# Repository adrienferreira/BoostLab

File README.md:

# BoostLab
DCDC step-down converter using only discrete components.

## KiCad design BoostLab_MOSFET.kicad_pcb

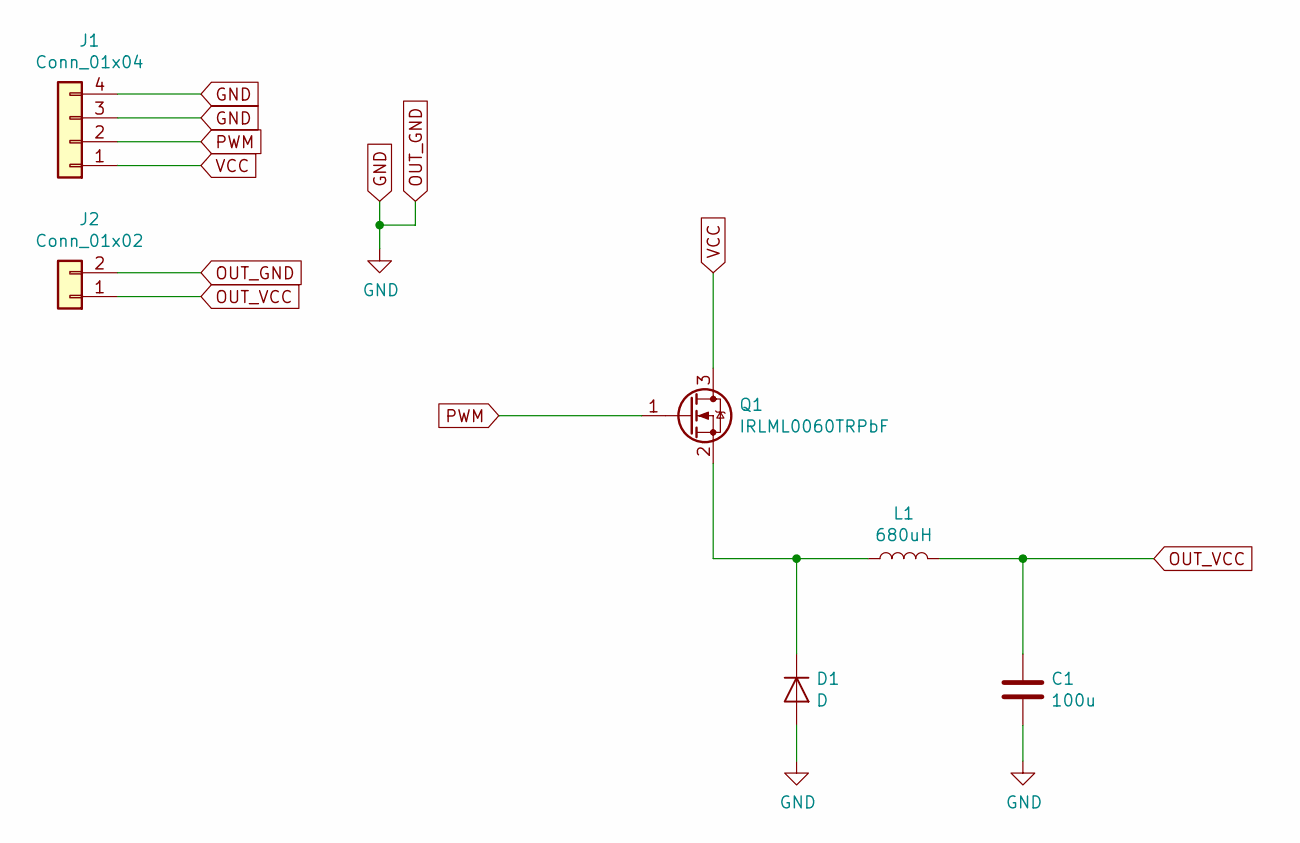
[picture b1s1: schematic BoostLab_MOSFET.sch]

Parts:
C1: 100u; C_1206_3216Metric_Pad1.42x1.75mm_HandSolder
D1: D; D_DO-41_SOD81_P10.16mm_Horizontal
J1: Conn_01x04; PinHeader_1x04_P2.54mm_Vertical
J2: Conn_01x02; PinHeader_1x02_P2.54mm_Vertical
L1: 680uH; L_Radial_D7.8mm_P5.00mm_Fastron_07HCP
Q1: IRLML0060TRPbF; SOT-23

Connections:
GND: C1.2, D1.2 (A), J1.3, J1.4, J2.2
unnamed: D1.1 (K), L1.1, Q1.2 (S)
OUT_VCC: C1.1, J2.1, L1.2
PWM: J1.2, Q1.1 (G)
VCC: J1.1, Q1.3 (D)

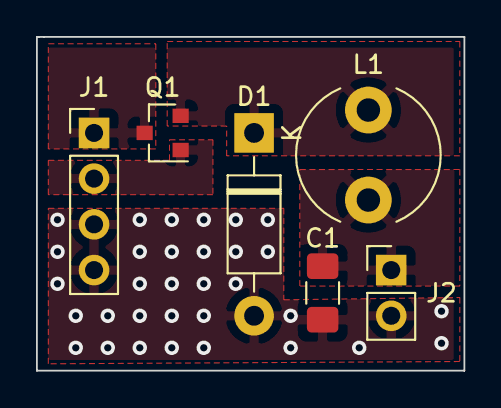
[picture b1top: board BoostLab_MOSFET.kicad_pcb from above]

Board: 2 copper layers, 23.7 x 18.5 mm, 6 parts (0 on the bottom side), 5 nets.

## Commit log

2020-01-28 Basic implementation SMPS, needs freq. generator
